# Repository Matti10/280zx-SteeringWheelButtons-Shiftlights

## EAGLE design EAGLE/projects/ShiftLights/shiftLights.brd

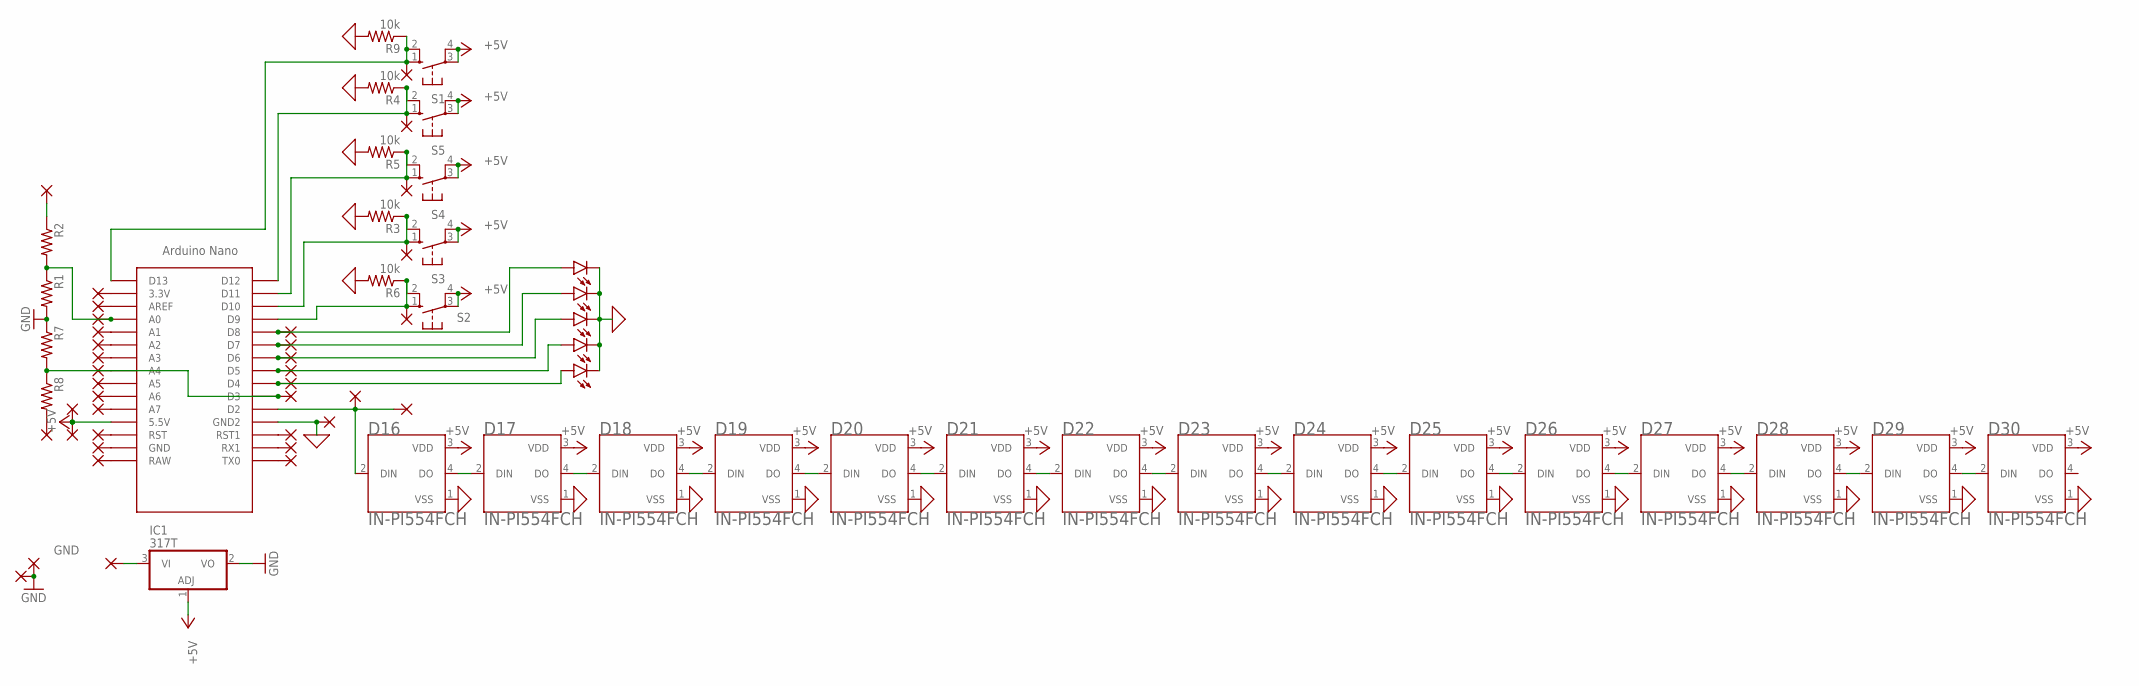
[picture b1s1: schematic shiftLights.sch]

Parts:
5V: 1,6/0,9
+12V: 1,6/0,9
D16, D17, D18, D19, D20, D21, D22, D23, D24, D25, D26, D27, D28, D29, D30: IN-PI554FCH; LED_IN-PI554FCH
DIM: 1,6/0,9
DIN: 1,6/0,9
GND: 1,6/0,9
GND4: GND; 1,6/0,9
IC1: 317T; TO220H
LED1, LED2, LED3, LED4, LED5: LED5MM
PAD1, PAD2, PAD3, PAD4, PAD5, PAD6, PAD7, PAD8, PAD9, PAD10, PAD11, PAD12, PAD13, PAD14, PAD15, PAD16, PAD17, PAD18, PAD19, PAD20, PAD21, PAD22, PAD23, PAD24, PAD25, PAD26, PAD27, PAD28, PAD29, PAD30: 1,6/0,9
R1, R2, R7, R8: R-US_0411/3V; 0411V
R3, R4, R5, R6, R9: 10k; 0411V
RPM: 1,6/0,9
S1, S2, S3, S4, S5: 10-XX; B3F-10XX
U$1: NANO

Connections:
0: D16.1 (VSS), D17.1 (VSS), D18.1 (VSS), D19.1 (VSS), D20.1 (VSS), D21.1 (VSS), D22.1 (VSS), D23.1 (VSS), D24.1 (VSS), D25.1 (VSS), D26.1 (VSS), D27.1 (VSS), D28.1 (VSS), D29.1 (VSS), D30.1 (VSS), LED1.K (C), LED2.K (C), LED3.K (C), LED4.K (C), LED5.K (C), PAD28.1, R3.2, R4.2, R5.2, R6.2, R9.2, U$1.GND1 (GND2)
+5V: 5V.1, D16.3 (VDD), D17.3 (VDD), D18.3 (VDD), D19.3 (VDD), D20.3 (VDD), D21.3 (VDD), D22.3 (VDD), D23.3 (VDD), D24.3 (VDD), D25.3 (VDD), D26.3 (VDD), D27.3 (VDD), D28.3 (VDD), D29.3 (VDD), D30.3 (VDD), IC1.1 (ADJ), PAD23.1, S1.3, S1.4 (P1), S2.3, S2.4 (P1), S3.3, S3.4 (P1), S4.3, S4.4 (P1), S5.3, S5.4 (P1), U$1.5V (5.5V)
GND: GND.1, GND4.1, IC1.2 (VO), R1.2, R7.1
unnamed: DIM.1, R2.1
unnamed: R8.2, RPM.1
unnamed: D16.4 (DO), D17.2 (DIN)
unnamed: D17.4 (DO), D18.2 (DIN)
unnamed: D16.2 (DIN), DIN.1, PAD29.1, U$1.D2
unnamed: PAD30.1, R7.2, R8.1, U$1.D3
unnamed: PAD1.1, U$1.A1
unnamed: PAD3.1, U$1.AREF
unnamed: LED1.A, PAD4.1, U$1.D8
unnamed: PAD5.1, U$1.3.3V
unnamed: LED3.A, PAD6.1, U$1.D6
unnamed: LED4.A, PAD7.1, U$1.D5
unnamed: LED5.A, PAD8.1, U$1.D4
unnamed: PAD9.1, U$1.RST1
unnamed: PAD10.1, U$1.RX1
unnamed: PAD11.1, U$1.TX0
unnamed: PAD2.1, R1.1, R2.2, U$1.A0
unnamed: PAD13.1, R6.1, S2.1 (S), S2.2 (S1), U$1.D9
unnamed: PAD12.1, R3.1, S3.1 (S), S3.2 (S1), U$1.D10
unnamed: PAD15.1, R5.1, S4.1 (S), S4.2 (S1), U$1.D11
unnamed: D18.4 (DO), D19.2 (DIN)
unnamed: PAD17.1, U$1.A2
unnamed: PAD18.1, U$1.A3
unnamed: PAD19.1, U$1.A4
unnamed: PAD20.1, U$1.A5
unnamed: PAD21.1, U$1.A6
unnamed: PAD22.1, U$1.A7
unnamed: +12V.1, IC1.3 (VI)
unnamed: PAD24.1, U$1.RST
unnamed: PAD25.1, U$1.GND
unnamed: PAD26.1, U$1.RAW
unnamed: LED2.A, PAD27.1, U$1.D7
unnamed: D19.4 (DO), D20.2 (DIN)
unnamed: PAD16.1, R4.1, S5.1 (S), S5.2 (S1), U$1.D12
unnamed: D20.4 (DO), D21.2 (DIN)
unnamed: D21.4 (DO), D22.2 (DIN)
unnamed: D22.4 (DO), D23.2 (DIN)
unnamed: PAD14.1, R9.1, S1.1 (S), S1.2 (S1), U$1.D13
unnamed: D23.4 (DO), D24.2 (DIN)
unnamed: D24.4 (DO), D25.2 (DIN)
unnamed: D25.4 (DO), D26.2 (DIN)
unnamed: D26.4 (DO), D27.2 (DIN)
unnamed: D27.4 (DO), D28.2 (DIN)
unnamed: D28.4 (DO), D29.2 (DIN)
unnamed: D29.4 (DO), D30.2 (DIN)

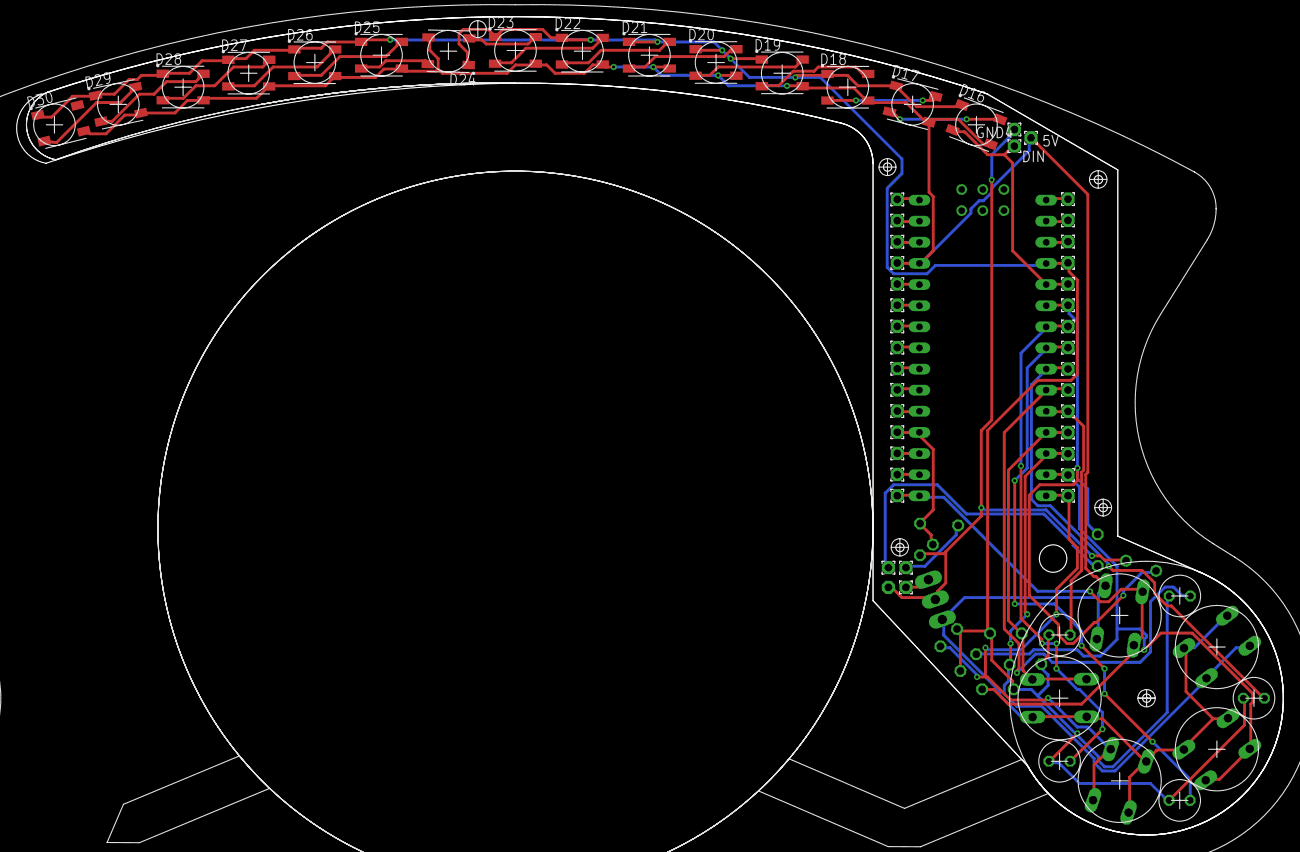
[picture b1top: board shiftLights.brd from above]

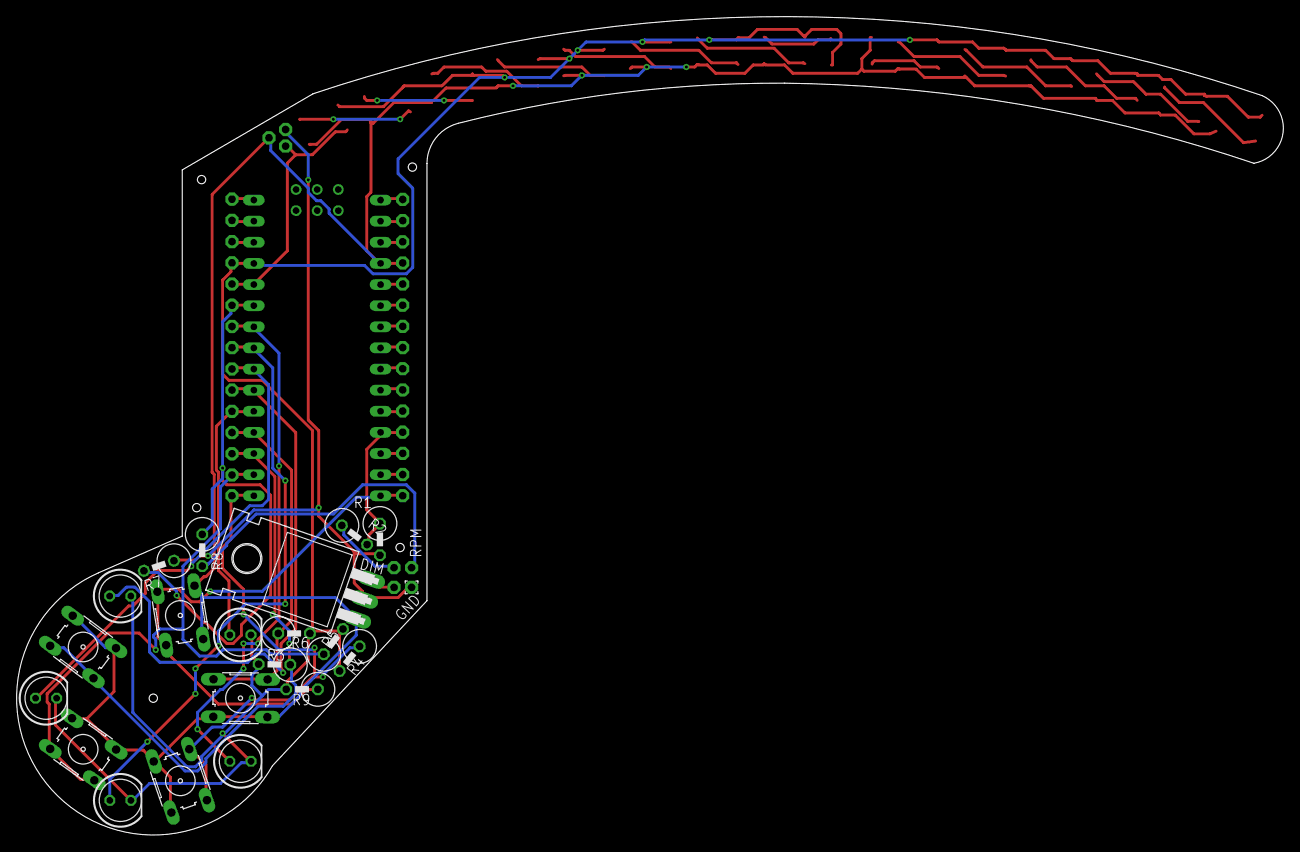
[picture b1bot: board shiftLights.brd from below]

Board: 2 copper layers, 152.3 x 98.4 mm, 73 parts (22 on the bottom side), 48 nets.

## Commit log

2024-12-16 adding old work
